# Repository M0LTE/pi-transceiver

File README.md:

# pi-transceiver
An attempt to build a complete ham radio transceiver around a Raspberry Pi

See [the wiki](https://github.com/M0LTE/pi-transceiver/wiki) for a more detailed project description / scratchlist of ideas / plans.

Also see [the open issues](https://github.com/M0LTE/pi-transceiver/issues) for stuff which needs working on. I've marked a few as Good First Issues.

[Discussions](https://github.com/M0LTE/pi-transceiver/discussions) is also a good place to ask questions / make comments / suggestions without raising an issue.

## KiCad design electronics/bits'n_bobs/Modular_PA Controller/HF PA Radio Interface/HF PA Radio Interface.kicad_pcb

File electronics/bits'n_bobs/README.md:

# Bits'n_bobs
This is a collection of small prototype modules and breakout boards to test various devices and features for the Pi Transceiver and similar projects.

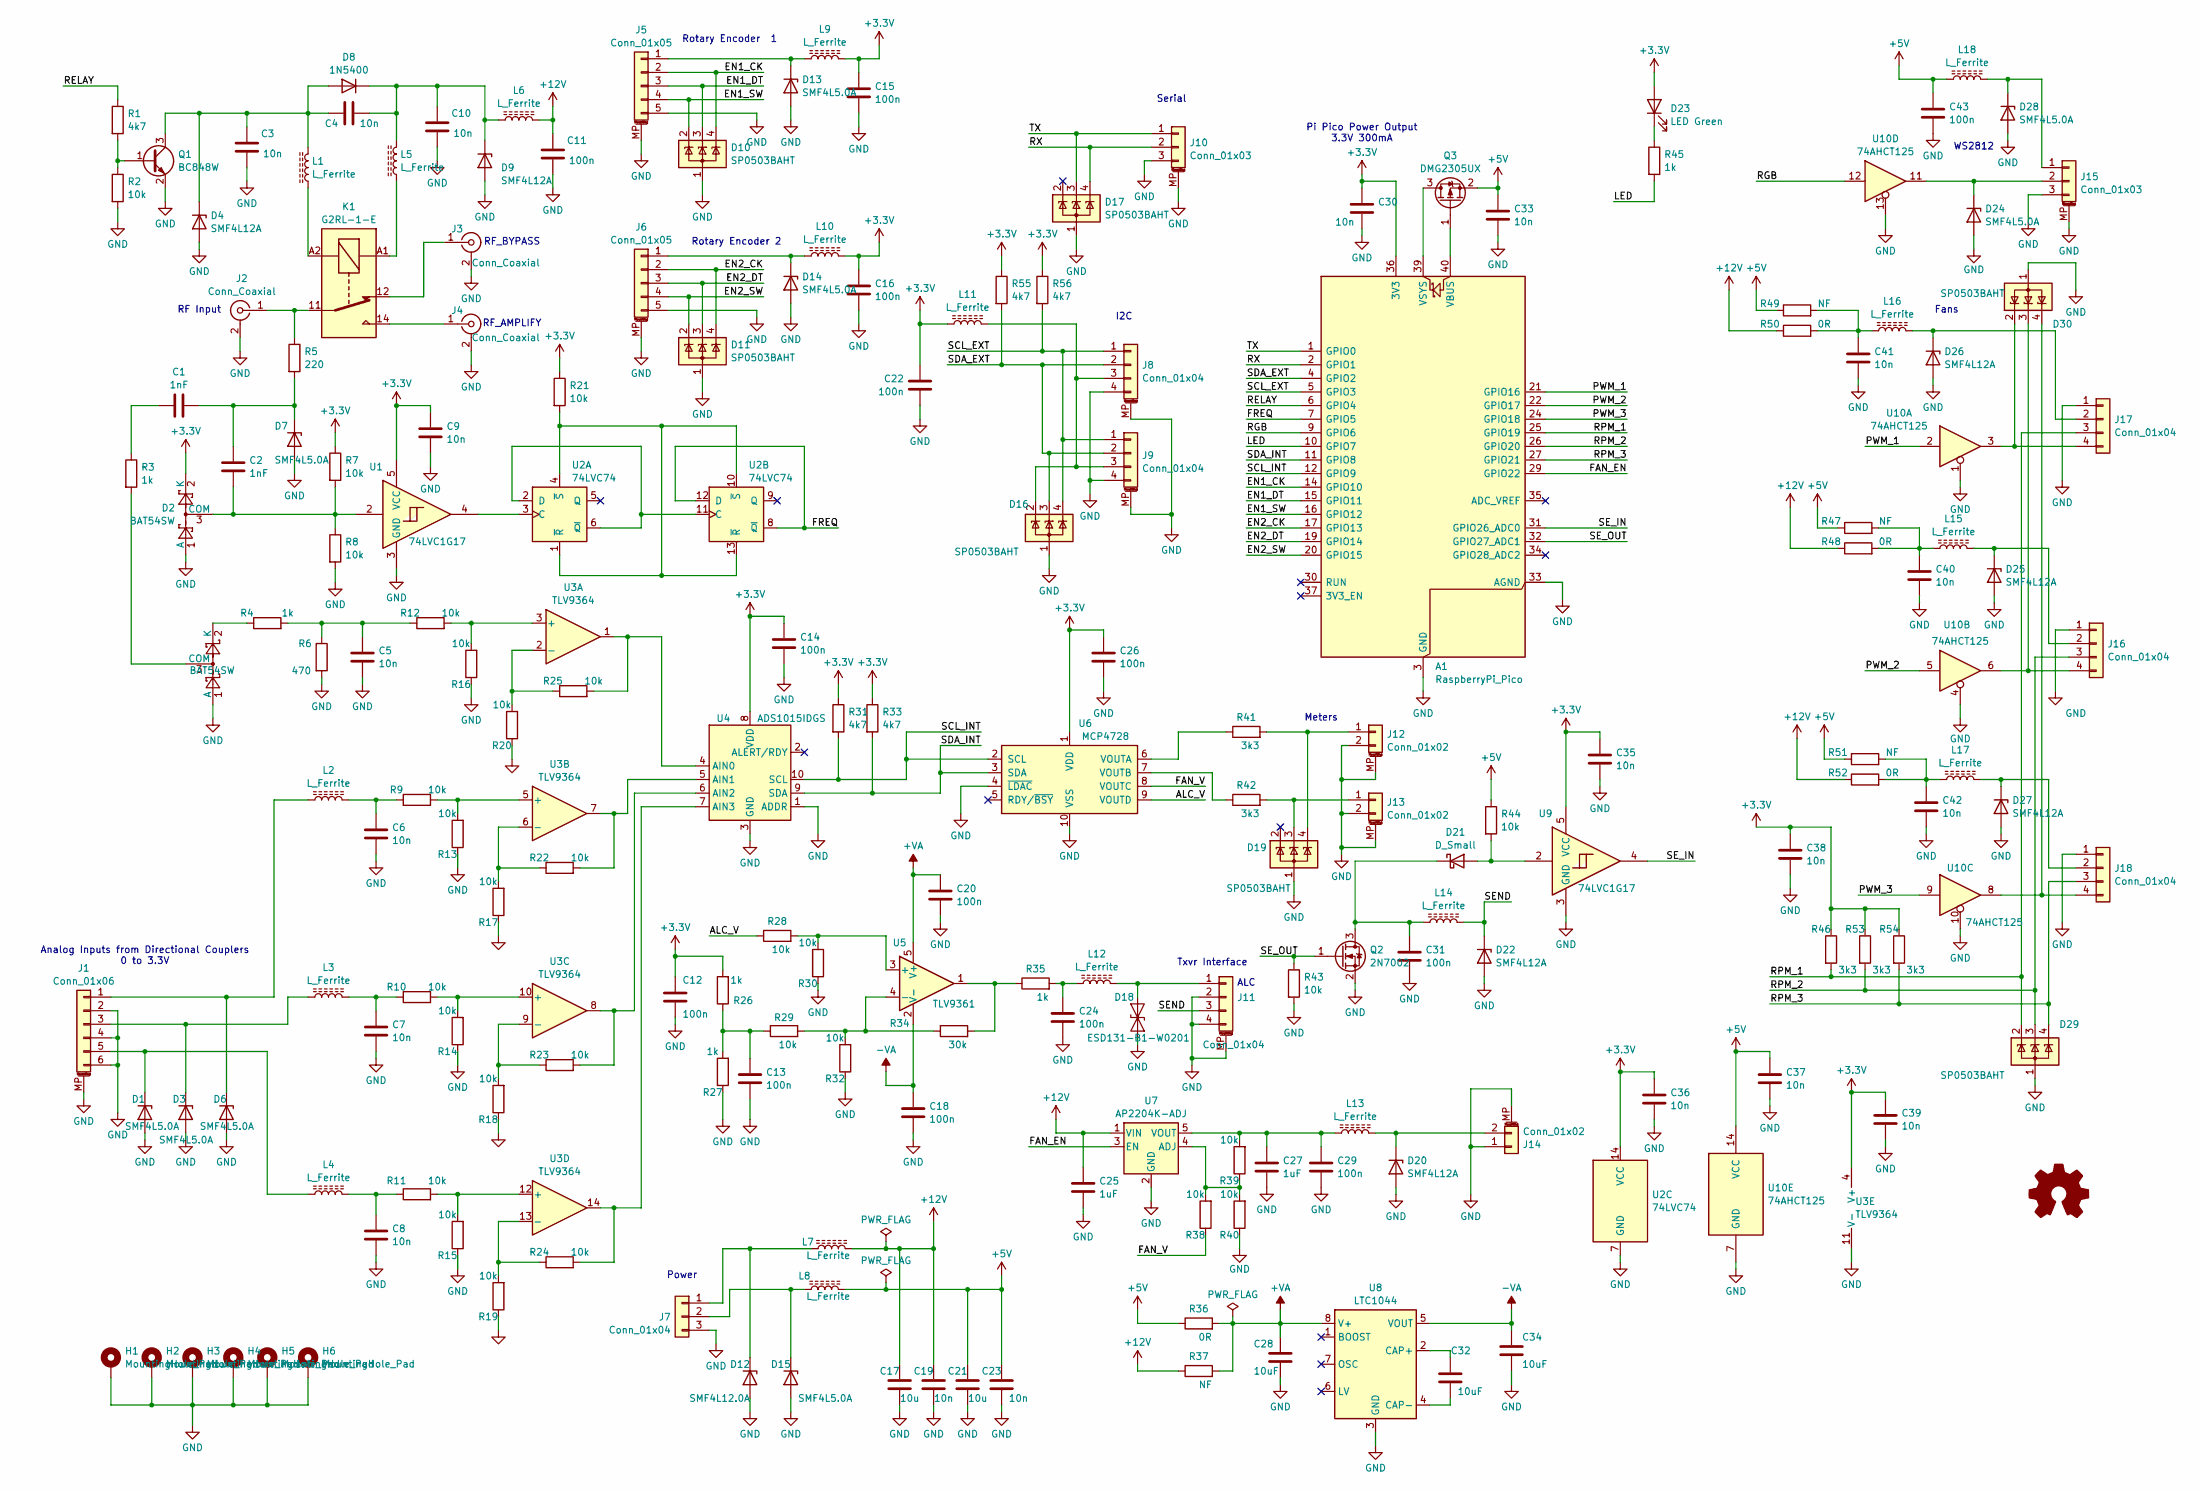
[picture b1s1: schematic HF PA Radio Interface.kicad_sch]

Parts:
A1: RaspberryPi_Pico; RPi_Pico_SMD_TH
C1, C2: 1nF; C_0603_1608Metric
C3, C4, C5, C6, C7, C8, C9, C10, C19, C23, C30, C33, C35, C36, C37, C38, C39, C40, C41, C42: 10n; C_0603_1608Metric
C11, C12, C13, C14, C15, C16, C18, C20, C22, C24, C26, C29, C31, C43: 100n; C_0603_1608Metric
C17, C21: 10u; C_0805_2012Metric
C25, C27: 1uF; C_0603_1608Metric
C28, C32, C34: 10uF; C_0603_1608Metric
D1, D3, D6, D7, D13, D14, D15, D24, D28: SMF4L5.0A; D_SOD-523
D2, D5: BAT54SW; SOT-323_SC-70
D4, D9, D20, D22, D25, D26, D27: SMF4L12A; D_SOD-523
D8: 1N5400; D_SOD-123
D10, D11, D16, D17, D19, D29, D30: SP0503BAHT; SOT-143
D12: SMF4L12.0A; D_SOD-523
D18: ESD131-B1-W0201; D_SOD-523
D21: D_Small; D_SOD-323
D23: LED Green; LED_0603_1608Metric
H1, H2, H3, H4, H5, H6: MountingHole_Pad; MountingHole_3.2mm_M3_DIN965_Pad
J1: Conn_01x06; JST_PH_S6B-PH-SM4-TB_1x06-1MP_P2.00mm_Horizontal
J2, J3, J4: Conn_Coaxial; SMA_Samtec_SMA-J-P-X-ST-EM1_EdgeMount
J5, J6: Conn_01x05; JST_PH_B5B-PH-SM4-TB_1x05-1MP_P2.00mm_Vertical
J7: Conn_01x04; JST_XH_S3B-XH-A_1x03_P2.50mm_Horizontal
J8, J9, J11: Conn_01x04; JST_PH_B4B-PH-SM4-TB_1x04-1MP_P2.00mm_Vertical
J10: Conn_01x03; JST_PH_B3B-PH-SM4-TB_1x03-1MP_P2.00mm_Vertical
J12, J13: Conn_01x02; JST_PH_B2B-PH-SM4-TB_1x02-1MP_P2.00mm_Vertical
J14: Conn_01x02; JST_PH_S2B-PH-SM4-TB_1x02-1MP_P2.00mm_Horizontal
J15: Conn_01x03; JST_PH_S3B-PH-SM4-TB_1x03-1MP_P2.00mm_Horizontal
J16, J17, J18: Conn_01x04; KF2510-4AW_3+1P
K1: G2RL-1-E; Relay_SPDT_Omron_G2RL-1-E
L1, L2, L3, L4, L5, L6, L7, L8, L9, L10, L11, L12, L13, L14, L15, L16, L17, L18: L_Ferrite; L_0603_1608Metric
Q1: BC848W; SOT-323_SC-70
Q2: 2N7002; SOT-23
Q3: DMG2305UX; SOT-23
R1, R31, R33, R55, R56: 4k7; R_0603_1608Metric
R2, R7, R8, R9, R10, R11, R12, R13, R14, R15, R16, R17, R18, R19, R20, R21, R22, R23, R24, R25, R28, R29, R30, R32, R38, R39, R40, R43, R44: 10k; R_0603_1608Metric
R3, R4, R26, R27, R35, R45: 1k; R_0603_1608Metric
R5: 220; R_0603_1608Metric
R6: 470; R_0603_1608Metric
R34: 30k; R_0603_1608Metric
R36, R48, R50, R52: 0R; R_0603_1608Metric
R37, R47, R49, R51: NF; R_0603_1608Metric
R41, R42, R46, R53, R54: 3k3; R_0603_1608Metric
SYM1: Logo_Open_Hardware_Small; OSHW-Logo2_7.3x6mm_SilkScreen
U1, U9: 74LVC1G17; SOT-353_SC-70-5
U2: 74LVC74; SOIC-14_3.9x8.7mm_P1.27mm
U3: TLV9364; SOIC-14_3.9x8.7mm_P1.27mm
U4: ADS1015IDGS; TSSOP-10_3x3mm_P0.5mm
U5: TLV9361; SOT-23-5
U6: MCP4728; MSOP-10_3x3mm_P0.5mm
U7: AP2204K-ADJ; SOT-23-5
U8: LTC1044; SOIC-8_5.23x5.23mm_P1.27mm
U10: 74AHCT125; TSSOP-14_4.4x5mm_P0.65mm

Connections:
+3.3V: A1.36 (3V3), C9.1, C12.1, C14.1, C15.1, C16.1, C22.1, C26.1, C30.1, C35.1, C36.1, C38.1, C39.1, D2.2 (K), D23.2 (A), L9.2, L10.2, L11.2, R7.1, R21.1, R26.2, R31.1, R33.1, R46.1, R53.1, R54.1, R55.1, R56.1, U1.5 (VCC), U2.14 (VCC), U3.4 (V+), U4.8 (VDD), U6.1 (VDD), U9.5 (VCC)
+5V: C21.1, C23.1, C33.1, C37.1, C43.1, L8.2, L18.1, Q3.2 (S), R36.1, R44.1, R47.1, R49.1, R51.1, U10.14 (VCC)
+12V: C11.1, C17.1, C19.1, C25.1, L6.2, L7.2, R37.1, R48.1, R50.1, R52.1, U7.1 (VIN)
+VA: C20.1, C28.1, R36.2, R37.2, U5.5 (V+), U8.8 (V+)
-VA: C18.1, C34.1, U5.2 (V-), U8.5 (VOUT)
/ALC_V: R28.1, U6.9 (VOUTD)
/EN1_CK: A1.14 (GPIO10), D10.4 (K), J5.2
/EN1_DT: A1.15 (GPIO11), D10.3 (K), J5.3
/EN1_SW: A1.16 (GPIO12), D10.2 (K), J5.4
/EN2_CK: A1.17 (GPIO13), D11.4 (K), J6.2
/EN2_DT: A1.19 (GPIO14), D11.3 (K), J6.3
/EN2_SW: A1.20 (GPIO15), D11.2 (K), J6.4
/FAN_EN: A1.29 (GPIO22), U7.3 (EN)
/FAN_V: R38.1, U6.8 (VOUTC)
/FREQ: A1.7 (GPIO5), U2.8 (~Q), U2.12 (D)
/LED: A1.10 (GPIO7), R45.2
/PWM_1: A1.21 (GPIO16), U10.2
/PWM_2: A1.22 (GPIO17), U10.5
/PWM_3: A1.24 (GPIO18), U10.9
/RELAY: A1.6 (GPIO4), R1.1
/RGB: A1.9 (GPIO6), U10.12
/RPM_1: A1.25 (GPIO19), D29.2 (K), J17.3, R46.2
/RPM_2: A1.26 (GPIO20), D29.3 (K), J16.3, R53.2
/RPM_3: A1.27 (GPIO21), D29.4 (K), J18.3, R54.2
/RX: A1.2 (GPIO1), D17.4 (K), J10.2
/SCL_EXT: A1.5 (GPIO3), D16.4 (K), J8.1, J9.1, R56.2
/SCL_INT: A1.12 (GPIO9), R31.2, U4.10 (SCL), U6.2 (SCL)
/SDA_EXT: A1.4 (GPIO2), D16.3 (K), J8.2, J9.2, R55.2
/SDA_INT: A1.11 (GPIO8), R33.2, U4.9 (SDA), U6.3 (SDA)
/SEND: D22.1 (K), J11.3, L14.2
/SE_IN: A1.31 (GPIO26_ADC0), U9.4
/SE_OUT: A1.32 (GPIO27_ADC1), Q2.1 (G), R43.1
/TX: A1.1 (GPIO0), D17.3 (K), J10.1
GND: A1.3 (GND), A1.8 (GND), A1.13 (GND), A1.18 (GND), A1.23 (GND), A1.28 (GND), A1.33 (AGND), A1.38 (GND), C3.2, C5.2, C6.2, C7.2, C8.2, C9.2, C10.2, C11.2, C12.2, C13.2, C14.2, C15.2, C16.2, C17.2, C18.2, C19.2, C20.2, C21.2, C22.2, C23.2, C24.2, C25.2, C26.2, C27.2, C28.2, C29.2, C30.2, C31.2, C33.2, C34.2, C35.2, C36.2, C37.2, C38.2, C39.2, C40.2, C41.2, C42.2, C43.2, D1.2 (A), D2.1 (A), D3.2 (A), D4.2 (A), D5.1 (A), D6.2 (A), D7.2 (A), D9.2 (A), D10.1 (A), D11.1 (A), D12.2 (A), D13.2 (A), D14.2 (A), D15.2 (A), D16.1 (A), D17.1 (A), D18.1 (A1), D19.1 (A), D20.2 (A), D22.2 (A), D24.2 (A), D25.2 (A), D26.2 (A), D27.2 (A), D28.2 (A), D29.1 (A), D30.1 (A), H1.1, H2.1, H3.1, H4.1, H5.1, H6.1, J1.2, J1.4, J1.6, J1.MP (MountPin), J2.2 (Ext), J3.2 (Ext), J4.2 (Ext), J5.5, J5.MP (MountPin), J6.5, J6.MP (MountPin), J7.3, J8.4, J8.MP (MountPin), J9.4, J9.MP (MountPin), J10.3, J10.MP (MountPin), J11.2, J11.4, J11.MP (MountPin), J12.2, J12.MP (MountPin), J13.2, J13.MP (MountPin), J14.1, J14.MP (MountPin), J15.3, J15.MP (MountPin), J16.1, J17.1, J18.1, Q1.2 (E), Q2.2 (S), R2.2, R6.2, R8.2, R13.1, R14.1, R15.1, R16.1, R17.1, R18.1, R19.1, R20.1, R27.1, R30.1, R32.1, R40.1, R43.2, U1.3 (GND), U2.7 (GND), U3.11 (V-), U4.1 (ADDR), U4.3 (GND), U6.4 (~LDAC), U6.10 (VSS), U7.2 (GND), U8.3 (GND), U9.3 (GND), U10.1, U10.4, U10.7 (GND), U10.10, U10.13
unnamed: A1.40 (VBUS), Q3.1 (G)
unnamed: A1.39 (VSYS), Q3.3 (D)
unnamed: C1.2, R3.1
unnamed: C5.1, R4.2, R6.1, R12.1
unnamed: C6.1, L2.2, R9.1
unnamed: C7.1, L3.2, R10.1
unnamed: C8.1, L4.2, R11.1
unnamed: C13.1, R26.1, R27.2, R29.1
unnamed: C24.1, L12.1, R35.2
unnamed: C40.1, L15.1, R47.2, R48.2
unnamed: C41.1, L16.1, R49.2, R50.2
unnamed: C42.1, L17.1, R51.2, R52.2
unnamed: D1.1 (K), J1.5, L4.1
unnamed: C2.2, D2.3 (COM), R7.2, R8.1, U1.2
unnamed: D3.1 (K), J1.3, L3.1
unnamed: C3.1, C4.1, D4.1 (K), D8.2 (A), L1.2, Q1.3 (C)
unnamed: D5.3 (COM), R3.2
unnamed: D5.2 (K), R4.1
unnamed: D6.1 (K), J1.1, L2.1
unnamed: C1.1, C2.1, D7.1 (K), R5.2
unnamed: C4.2, C10.1, D8.1 (K), D9.1 (K), L5.2, L6.1
unnamed: D12.1 (K), J7.1, L7.1
unnamed: D13.1 (K), J5.1, L9.1
unnamed: D14.1 (K), J6.1, L10.1
unnamed: D15.1 (K), J7.2, L8.1
unnamed: D18.2 (A2), J11.1, L12.2
unnamed: D20.1 (K), J14.2, L13.2
unnamed: D21.2 (A), R44.2, U9.2
unnamed: C31.1, D21.1 (K), L14.1, Q2.3 (D)
unnamed: D23.1 (K), R45.1
unnamed: D24.1 (K), J15.2, U10.11
unnamed: D25.1 (K), J16.2, L15.2
unnamed: D26.1 (K), J17.2, L16.2
unnamed: D27.1 (K), J18.2, L17.2
unnamed: D28.1 (K), J15.1, L18.2
unnamed: J2.1 (In), K1.11, R5.1
unnamed: J3.1 (In), K1.12
unnamed: J4.1 (In), K1.14
unnamed: D16.2 (K), J8.3, J9.3, L11.1
unnamed: D19.4 (K), J12.1, R41.2
unnamed: D19.3 (K), J13.1, R42.2
unnamed: D30.3 (K), J16.4, U10.6
unnamed: D30.2 (K), J17.4, U10.3
unnamed: D30.4 (K), J18.4, U10.8
unnamed: K1.A1, L5.1
unnamed: K1.A2, L1.1
unnamed: Q1.1 (B), R1.2, R2.1
unnamed: R34.2, R35.1, U5.1
unnamed: U1.4, U2.3 (C)
unnamed: U2.2 (D), U2.6 (~Q), U2.11 (C)
unnamed: R21.2, U2.1 (~R), U2.4 (~S), U2.10 (~S), U2.13 (~R)
unnamed: R12.2, R16.2, U3.3 (+)
unnamed: R20.2, R25.1, U3.2 (-)
unnamed: R9.2, R13.2, U3.5 (+)
unnamed: R17.2, R22.1, U3.6 (-)
unnamed: R10.2, R14.2, U3.10 (+)
unnamed: R18.2, R23.1, U3.9 (-)
unnamed: R11.2, R15.2, U3.12 (+)
unnamed: R19.2, R24.1, U3.13 (-)
unnamed: R25.2, U3.1, U4.4 (AIN0)
unnamed: R22.2, U3.7, U4.5 (AIN1)
unnamed: R23.2, U3.8, U4.6 (AIN2)
unnamed: R24.2, U3.14, U4.7 (AIN3)
unnamed: R28.2, R30.2, U5.3 (+)
unnamed: R29.2, R32.2, R34.1, U5.4 (-)
unnamed: R41.1, U6.6 (VOUTA)
unnamed: R42.1, U6.7 (VOUTB)
unnamed: R38.2, R39.1, R40.2, U7.4 (ADJ)
unnamed: C27.1, C29.1, L13.1, R39.2, U7.5 (VOUT)
unnamed: C32.1, U8.2 (CAP+)
unnamed: C32.2, U8.4 (CAP-)

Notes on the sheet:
Rotary Encoder 2
RF Input
Fans
Txvr Interface
ALC
RF_BYPASS
Serial
RF_AMPLIFY
Rotary Encoder 1
Analog Inputs from Directional Couplers 0 to 3.3V
Power
Meters
WS2812
Pi Pico Power Output 3.3V 300mA
I2C

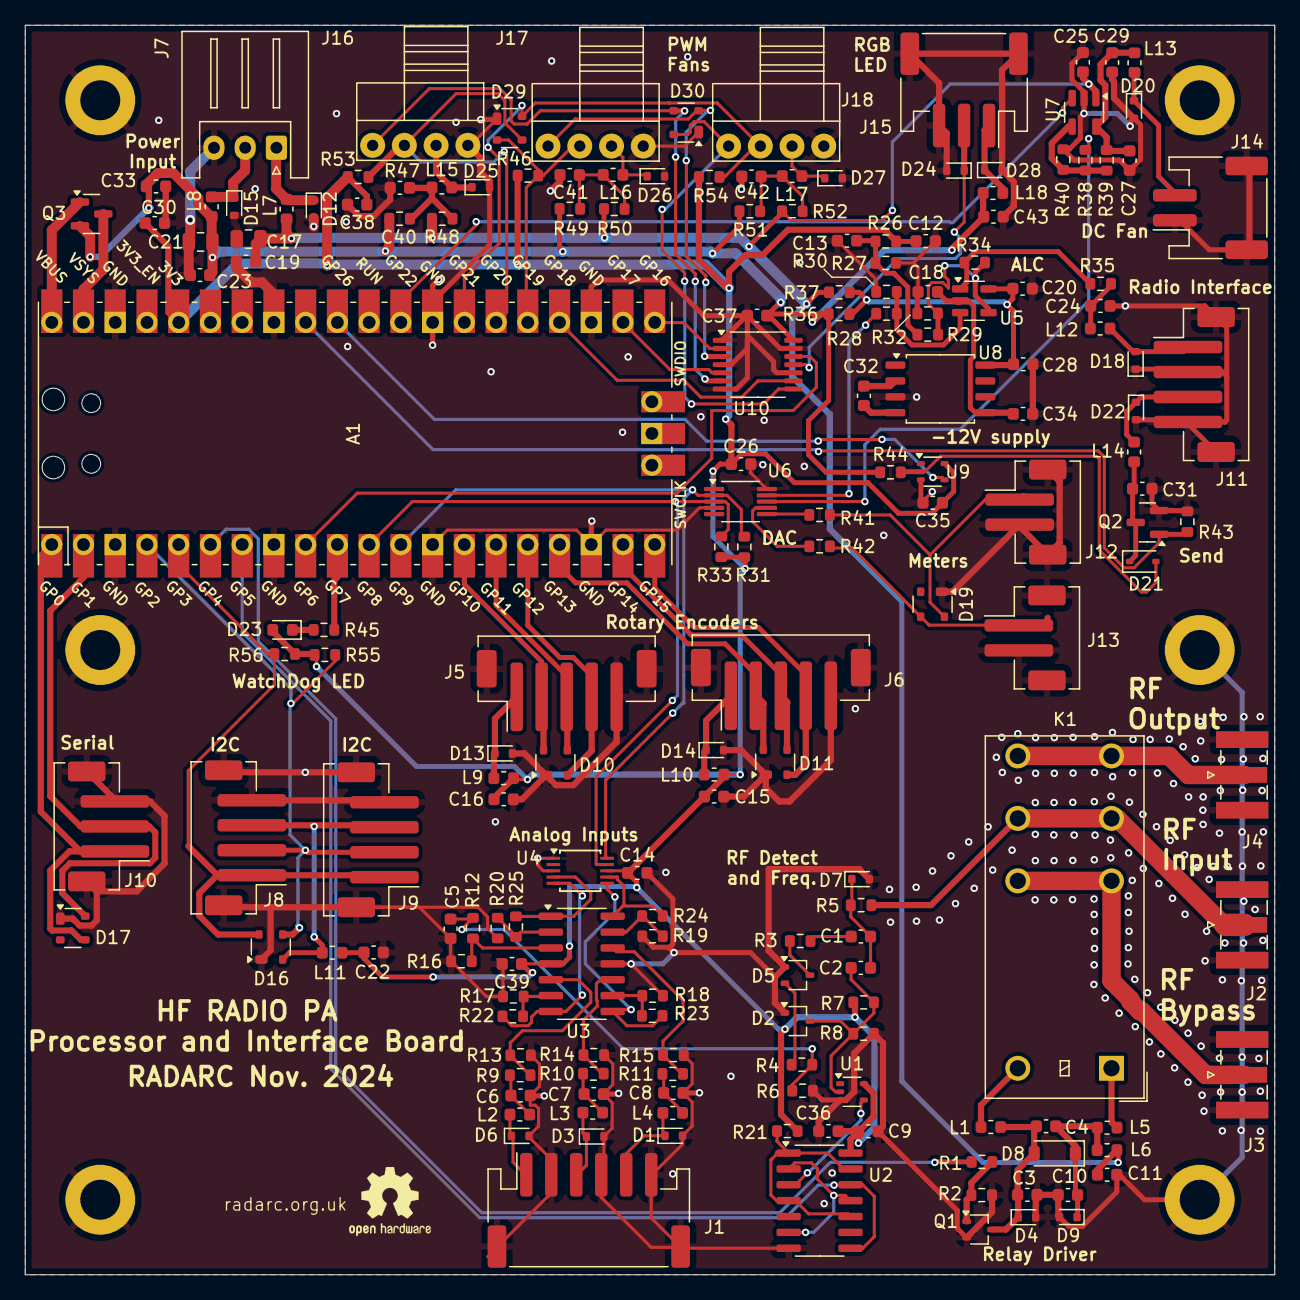
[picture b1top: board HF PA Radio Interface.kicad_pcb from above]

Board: 2 copper layers, 100.0 x 100.0 mm, 187 parts (0 on the bottom side), 105 nets.

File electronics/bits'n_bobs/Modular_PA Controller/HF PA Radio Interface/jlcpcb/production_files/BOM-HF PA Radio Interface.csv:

Comment,Designator,Footprint,LCSC
Conn_Coaxial,"J2,J3,J4",SMA_Samtec_SMA-J-P-X-ST-EM1_EdgeMount,C1509221
10k,R22,R_0603_1608Metric,
10k,R29,R_0603_1608Metric,
LTC1044,U8,SOIC-8_5.23x5.23mm_P1.27mm,
10n,C5,C_0603_1608Metric,
L_Ferrite,L17,L_0603_1608Metric,
10uF,C28,C_0603_1608Metric,
MCP4728,U6,MSOP-10_3x3mm_P0.5mm,
G2RL-1-E,K1,Relay_SPDT_Omron_G2RL-1-E,
10k,R9,R_0603_1608Metric,
3k3,R42,R_0603_1608Metric,
10k,R12,R_0603_1608Metric,
1N5400,D8,D_SOD-123,
SP0503BAHT,D10,SOT-143,
Conn_01x04,J7,JST_XH_S3B-XH-A_1x03_P2.50mm_Horizontal,
NF,R47,R_0603_1608Metric,
30k,R34,R_0603_1608Metric,
0R,R52,R_0603_1608Metric,
3k3,R53,R_0603_1608Metric,
Conn_01x03,J15,JST_PH_S3B-PH-SM4-TB_1x03-1MP_P2.00mm_Horizontal,
1k,R26,R_0603_1608Metric,
L_Ferrite,L4,L_0603_1608Metric,
100n,C14,C_0603_1608Metric,
10k,R30,R_0603_1608Metric,
10k,R11,R_0603_1608Metric,
1k,R27,R_0603_1608Metric,
100n,C31,C_0603_1608Metric,
D_Small,D21,D_SOD-323,
Conn_01x04,J9,JST_PH_B4B-PH-SM4-TB_1x04-1MP_P2.00mm_Vertical,
SP0503BAHT,D19,SOT-143,
NF,R49,R_0603_1608Metric,
Conn_01x04,J8,JST_PH_B4B-PH-SM4-TB_1x04-1MP_P2.00mm_Vertical,
10k,R40,R_0603_1608Metric,
L_Ferrite,L2,L_0603_1608Metric,
10n,C38,C_0603_1608Metric,
Conn_01x04,J16,KF2510-4AW_3+1P,
Conn_01x05,J6,JST_PH_B5B-PH-SM4-TB_1x05-1MP_P2.00mm_Vertical,
SP0503BAHT,D17,SOT-143,
4k7,R56,R_0603_1608Metric,
Conn_01x03,J10,JST_PH_B3B-PH-SM4-TB_1x03-1MP_P2.00mm_Vertical,
SMF4L12A,D27,D_SOD-523,
10k,R8,R_0603_1608Metric,
Conn_01x04,J18,KF2510-4AW_3+1P,
10k,R18,R_0603_1608Metric,
74LVC1G17,U9,SOT-353_SC-70-5,
10k,R13,R_0603_1608Metric,
10k,R10,R_0603_1608Metric,
L_Ferrite,L8,L_0603_1608Metric,
L_Ferrite,L12,L_0603_1608Metric,
L_Ferrite,L16,L_0603_1608Metric,
4k7,R33,R_0603_1608Metric,
10n,C23,C_0603_1608Metric,
100n,C24,C_0603_1608Metric,
L_Ferrite,L6,L_0603_1608Metric,
4k7,R31,R_0603_1608Metric,
RaspberryPi_Pico,A1,RPi_Pico_SMD_TH,
AP2204K-ADJ,U7,SOT-23-5,
SMF4L12A,D25,D_SOD-523,
10uF,C34,C_0603_1608Metric,
10k,R16,R_0603_1608Metric,
10n,C39,C_0603_1608Metric,
BAT54SW,D5,SOT-323_SC-70,
SMF4L12A,D4,D_SOD-523,
3k3,R41,R_0603_1608Metric,
Conn_01x06,J1,JST_PH_S6B-PH-SM4-TB_1x06-1MP_P2.00mm_Horizontal,
10n,C40,C_0603_1608Metric,
L_Ferrite,L15,L_0603_1608Metric,
100n,C12,C_0603_1608Metric,
SP0503BAHT,D29,SOT-143,
470,R6,R_0603_1608Metric,
100n,C16,C_0603_1608Metric,
10n,C4,C_0603_1608Metric,
100n,C26,C_0603_1608Metric,
2N7002,Q2,SOT-23,
10n,C42,C_0603_1608Metric,
10k,R23,R_0603_1608Metric,
L_Ferrite,L3,L_0603_1608Metric,
L_Ferrite,L14,L_0603_1608Metric,
SMF4L5.0A,D3,D_SOD-523,
SP0503BAHT,D16,SOT-143,
10n,C19,C_0603_1608Metric,
10n,C9,C_0603_1608Metric,
10k,R39,R_0603_1608Metric,
10n,C6,C_0603_1608Metric,
10n,C8,C_0603_1608Metric,
1k,R4,R_0603_1608Metric,
SMF4L12A,D26,D_SOD-523,
SMF4L5.0A,D24,D_SOD-523,
0R,R50,R_0603_1608Metric,
1uF,C25,C_0603_1608Metric,
10k,R43,R_0603_1608Metric,
Conn_01x05,J5,JST_PH_B5B-PH-SM4-TB_1x05-1MP_P2.00mm_Vertical,
10n,C33,C_0603_1608Metric,
10n,C35,C_0603_1608Metric,
L_Ferrite,L11,L_0603_1608Metric,
220,R5,R_0603_1608Metric,
L_Ferrite,L10,L_0603_1608Metric,
10k,R25,R_0603_1608Metric,
BAT54SW,D2,SOT-323_SC-70,
10k,R38,R_0603_1608Metric,
L_Ferrite,L1,L_0603_1608Metric,
SMF4L12A,D9,D_SOD-523,
Conn_01x02,J14,JST_PH_S2B-PH-SM4-TB_1x02-1MP_P2.00mm_Horizontal,
TLV9361,U5,SOT-23-5,
1nF,C2,C_0603_1608Metric,
LED Green,D23,LED_0603_1608Metric,
10n,C41,C_0603_1608Metric,
100n,C29,C_0603_1608Metric,
100n,C22,C_0603_1608Metric,
10k,R14,R_0603_1608Metric,
L_Ferrite,L9,L_0603_1608Metric,
100n,C18,C_0603_1608Metric,
SMF4L5.0A,D7,D_SOD-523,
SMF4L12A,D20,D_SOD-523,
10k,R21,R_0603_1608Metric,
10n,C37,C_0603_1608Metric,
L_Ferrite,L18,L_0603_1608Metric,
SMF4L5.0A,D6,D_SOD-523,
74LVC1G17,U1,SOT-353_SC-70-5,
3k3,R54,R_0603_1608Metric,
Conn_01x02,J13,JST_PH_B2B-PH-SM4-TB_1x02-1MP_P2.00mm_Vertical,
SP0503BAHT,D30,SOT-143,
NF,R51,R_0603_1608Metric,
L_Ferrite,L13,L_0603_1608Metric,
1k,R35,R_0603_1608Metric,
10k,R28,R_0603_1608Metric,
10u,C21,C_0805_2012Metric,
10n,C3,C_0603_1608Metric,
DMG2305UX,Q3,SOT-23,
1nF,C1,C_0603_1608Metric,
SMF4L5.0A,D1,D_SOD-523,
4k7,R1,R_0603_1608Metric,
3k3,R46,R_0603_1608Metric,
100n,C15,C_0603_1608Metric,
10n,C36,C_0603_1608Metric,
10uF,C32,C_0603_1608Metric,
100n,C20,C_0603_1608Metric,
10k,R24,R_0603_1608Metric,
10n,C7,C_0603_1608Metric,
SMF4L5.0A,D14,D_SOD-523,
10k,R15,R_0603_1608Metric,
SMF4L12A,D22,D_SOD-523,
10k,R20,R_0603_1608Metric,
L_Ferrite,L5,L_0603_1608Metric,
10k,R2,R_0603_1608Metric,
100n,C11,C_0603_1608Metric,
0R,R36,R_0603_1608Metric,
Conn_01x02,J12,JST_PH_B2B-PH-SM4-TB_1x02-1MP_P2.00mm_Vertical,
10k,R7,R_0603_1608Metric,
100n,C13,C_0603_1608Metric,
Conn_01x04,J17,KF2510-4AW_3+1P,
ADS1015IDGS,U4,TSSOP-10_3x3mm_P0.5mm,
4k7,R55,R_0603_1608Metric,
SP0503BAHT,D11,SOT-143,
0R,R48,R_0603_1608Metric,
ESD131-B1-W0201,D18,D_SOD-523,
SMF4L5.0A,D13,D_SOD-523,
10k,R19,R_0603_1608Metric,
TLV9364,U3,SOIC-14_3.9x8.7mm_P1.27mm,
10k,R32,R_0603_1608Metric,
10n,C10,C_0603_1608Metric,
SMF4L12.0A,D12,D_SOD-523,
SMF4L5.0A,D28,D_SOD-523,
SMF4L5.0A,D15,D_SOD-523,
10u,C17,C_0805_2012Metric,
10n,C30,C_0603_1608Metric,
L_Ferrite,L7,L_0603_1608Metric,
BC848W,Q1,SOT-323_SC-70,
1k,R45,R_0603_1608Metric,
NF,R37,R_0603_1608Metric,
100n,C43,C_0603_1608Metric,
74LVC74,U2,SOIC-14_3.9x8.7mm_P1.27mm,
74AHCT125,U10,TSSOP-14_4.4x5mm_P0.65mm,
1k,R3,R_0603_1608Metric,
10k,R44,R_0603_1608Metric,
1uF,C27,C_0603_1608Metric,
10k,R17,R_0603_1608Metric,
Conn_01x04,J11,JST_PH_B4B-PH-SM4-TB_1x04-1MP_P2.00mm_Vertical,

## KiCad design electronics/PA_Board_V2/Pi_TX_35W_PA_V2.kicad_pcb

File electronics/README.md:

# pi-transceiver / electronics
Here is a folder for electronics parts of the Pi transceiver, e.g. PCBs

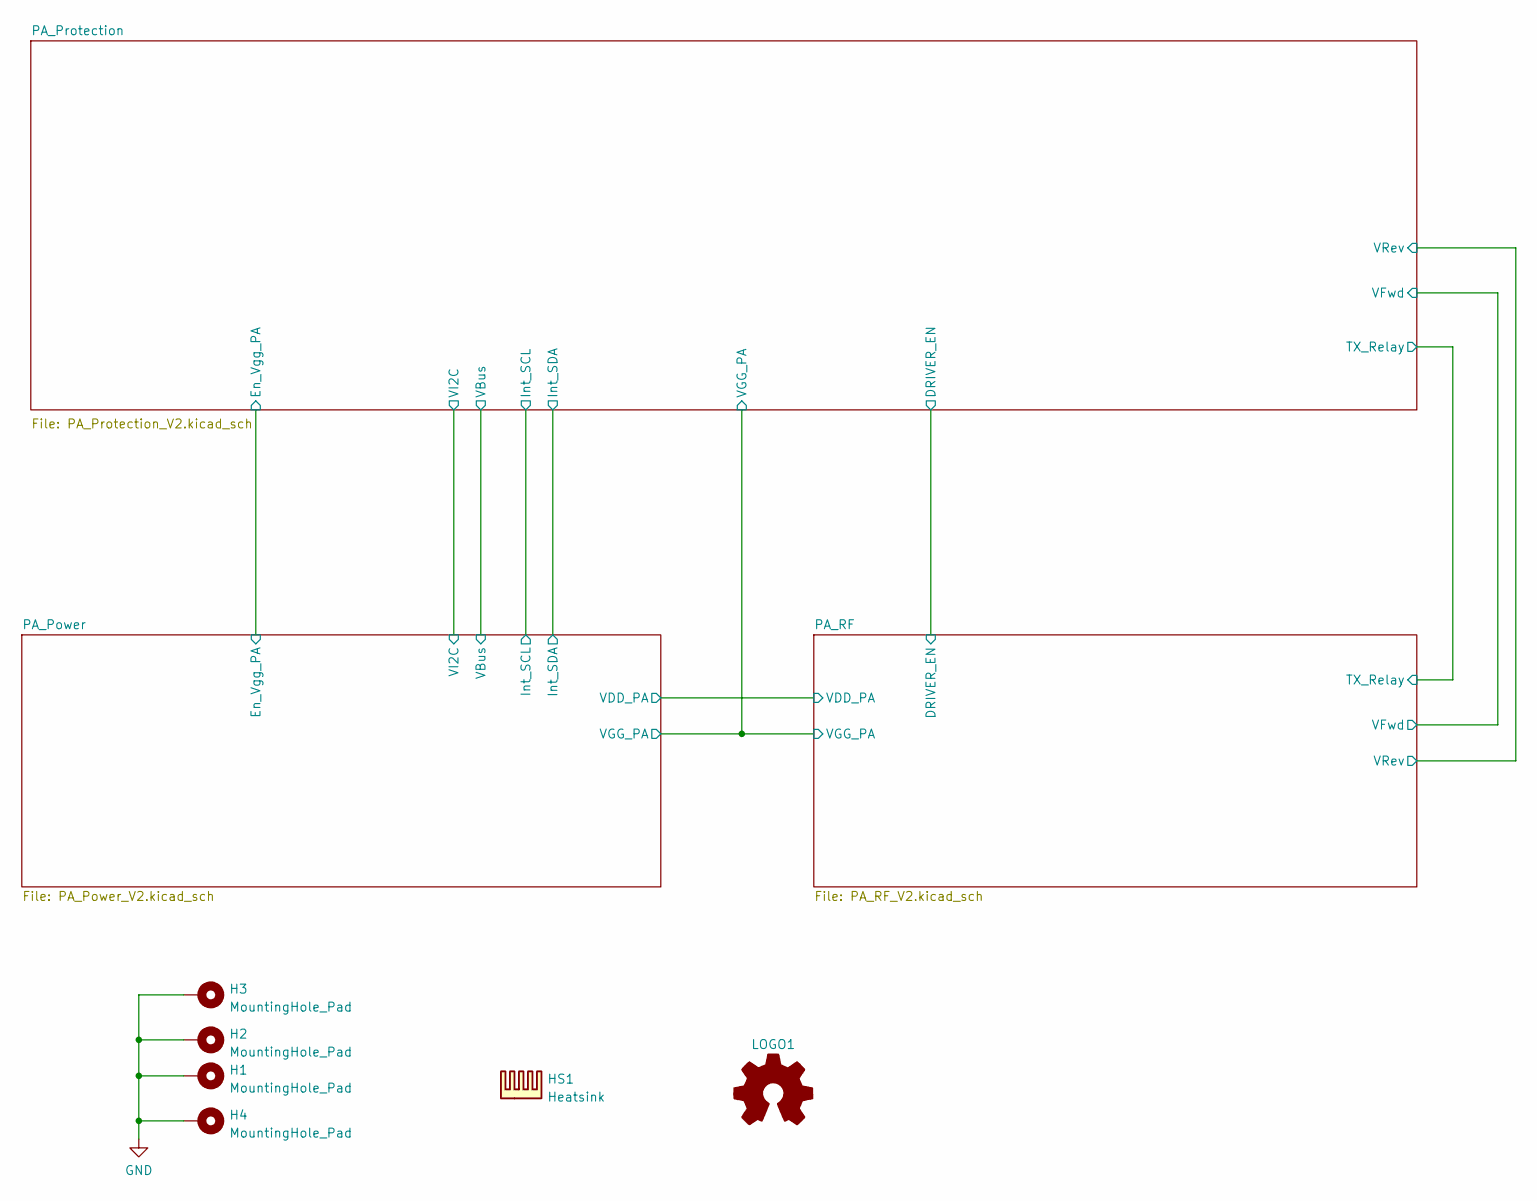
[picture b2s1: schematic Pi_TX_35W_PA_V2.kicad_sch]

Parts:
H1, H2, H3, H4: MountingHole_Pad; MountingHole_3.2mm_M3_DIN965_Pad
HS1: Heatsink; Copper_Pad
LOGO1: Logo_Open_Hardware_Small; OSHW-Logo2_9.8x8mm_SilkScreen

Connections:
GND: H1.1, H2.1, H3.1, H4.1; also elsewhere on the board

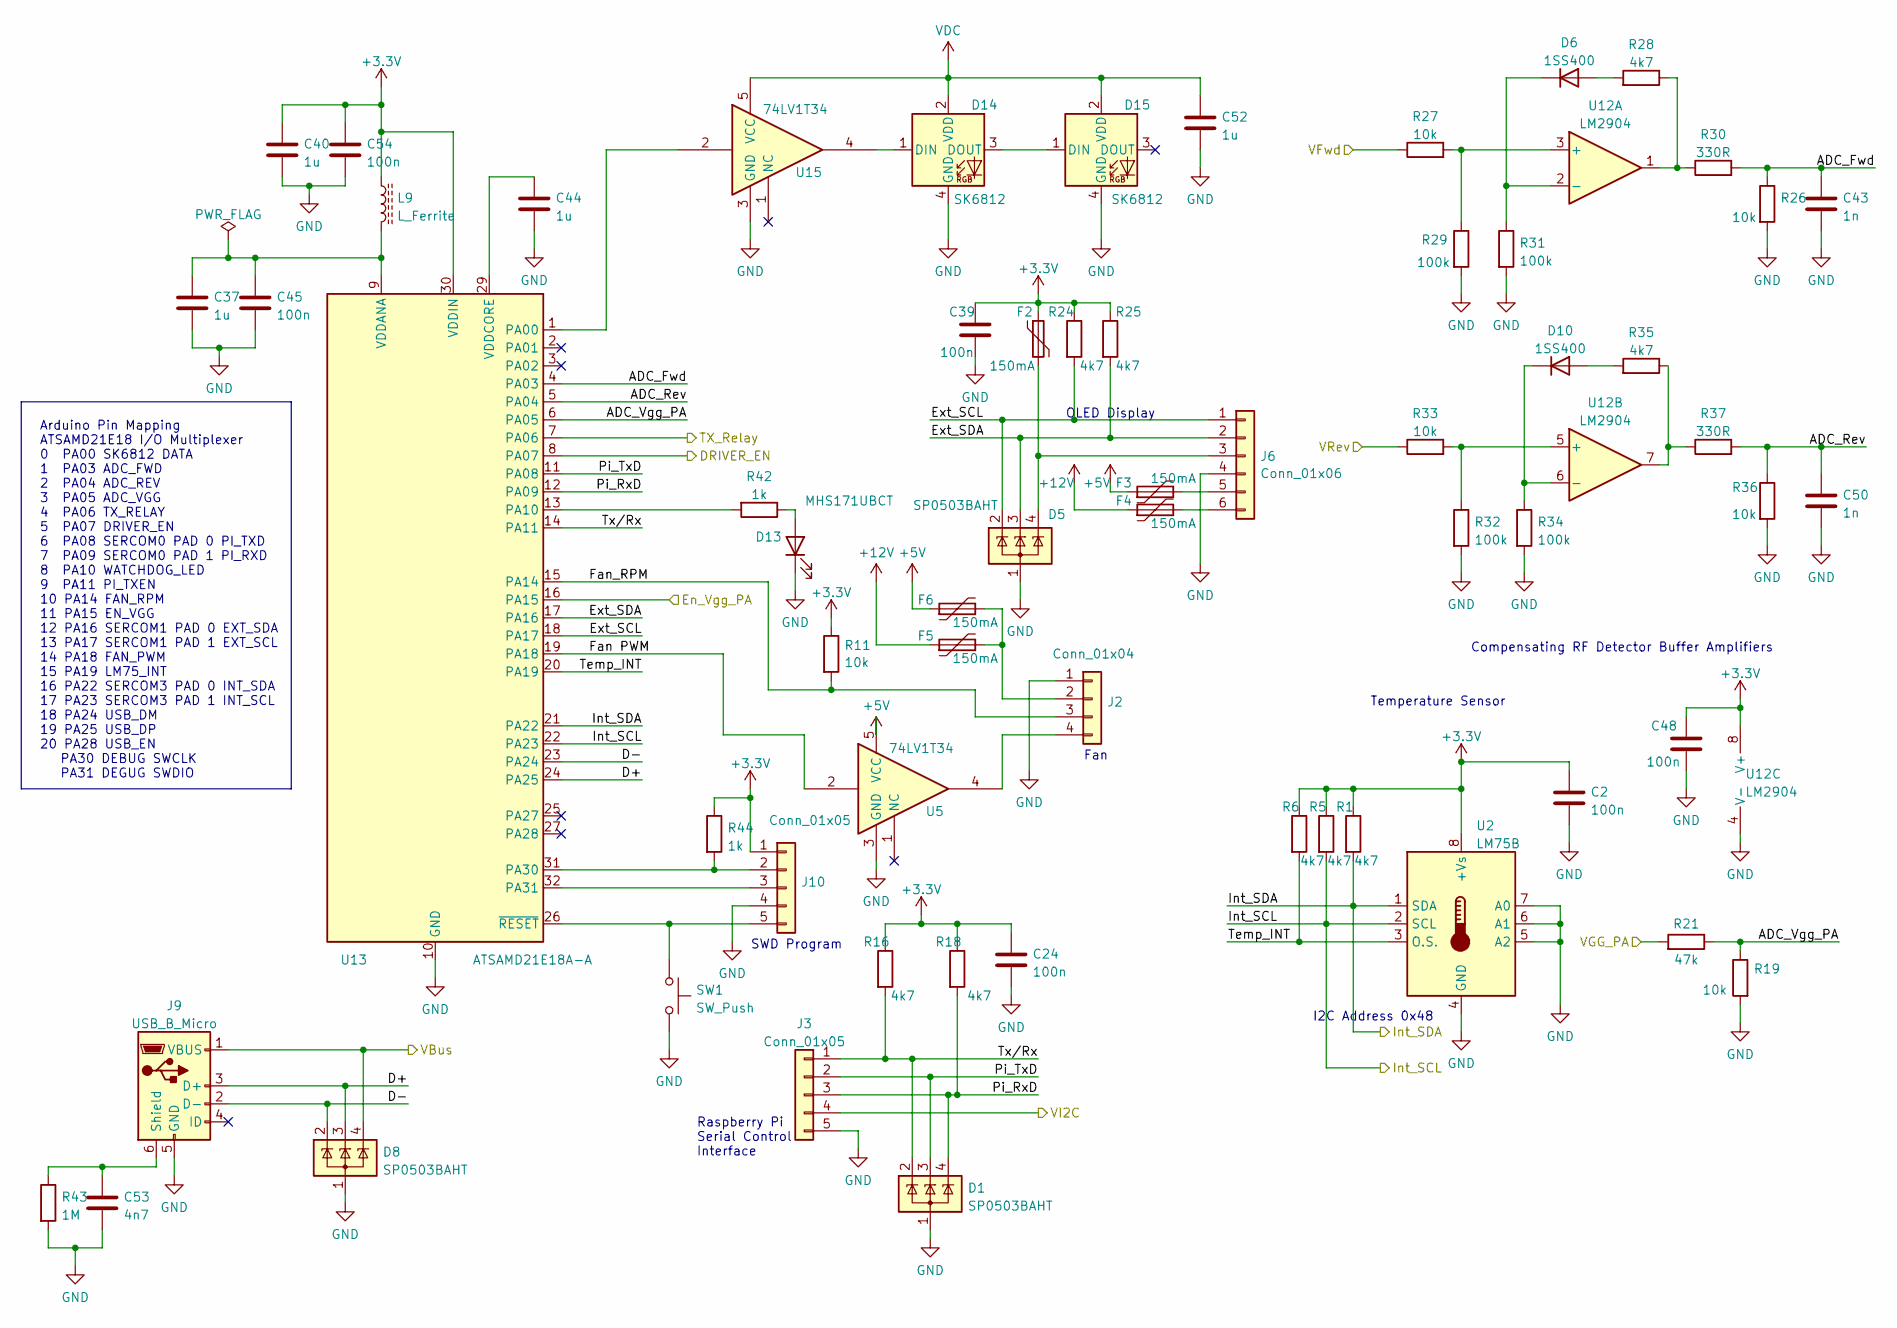
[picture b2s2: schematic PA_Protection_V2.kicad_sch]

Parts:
C2, C24, C39, C45, C48, C54: 100n; C_0603_1608Metric; LCSC Part C88136
C37, C40, C44, C52: 1u; C_0603_1608Metric; LCSC Part C89376
C43, C50: 1n; C_0603_1608Metric; LCSC Part C2839443
C53: 4n7; C_0603_1608Metric; LCSC Part C576815
D1, D5, D8: SP0503BAHT; SOT-143; LCSC Part C2682275
D6, D10: 1SS400; D_SOD-523; LCSC Part C68951
D13: MHS171UBCT; MHS171; LCSC Part C693906
D14, D15: SK6812; SK6812SIDE-A-RVS; LCSC Part C2890037
F2, F3, F4, F5, F6: 150mA; Fuse_0805_2012Metric; LCSC Part C2840556
J2: Conn_01x04; KF2510-4AW_3+1P
J3: Conn_01x05; JST_PH_S5B-PH-SM4-TB_1x05-1MP_P2.00mm_Horizontal; LCSC Part C7429692
J6: Conn_01x06; JST_PH_S6B-PH-SM4-TB_1x06-1MP_P2.00mm_Horizontal; LCSC Part C7429693
J9: USB_B_Micro; USB_Micro-B_Molex-105017-0001; LCSC Part C136000
J10: Conn_01x05; Debug_Clip
L9: L_Ferrite; L_0603_1608Metric; LCSC Part C98298
R1, R5, R6, R16, R18, R24, R25, R28, R35: 4k7; R_0603_1608Metric; LCSC Part C23162
R11, R19, R26, R27, R33, R36: 10k; R_0603_1608Metric; LCSC Part C25804
R21: 47k; R_0603_1608Metric; LCSC Part C25819
R29, R31, R32, R34: 100k; R_0603_1608Metric; LCSC Part C25803
R30, R37: 330R; R_0603_1608Metric; LCSC Part C23138
R42, R44: 1k; R_0603_1608Metric; LCSC Part C21190
R43: 1M; R_0603_1608Metric; LCSC Part C22935
SW1: SW_Push; Panasonic_EVQPUK_EVQPUB; LCSC Part C526225
U2: LM75B; SOIC-8_3.9x4.9mm_P1.27mm; LCSC Part C725792
U5, U15: 74LV1T34; SOT-353_SC-70-5; LCSC Part C5199768
U12: LM2904; SOIC-8_3.9x4.9mm_P1.27mm; LCSC Part C2941725
U13: ATSAMD21E18A-A; TQFP-32_7x7mm_P0.8mm; LCSC Part C618770

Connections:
+3.3V: C2.1, C24.1, C39.1, C40.1, C48.1, C54.1, F2.1, J10.1, L9.1, R1.1, R5.1, R6.1, R11.1, R16.1, R18.1, R24.1, R25.1, R44.1, U2.8 (+Vs), U12.8 (V+), U13.30 (VDDIN); also elsewhere on the board
+5V: F3.1, F6.1, U5.5 (VCC); also elsewhere on the board
+12V: F4.1, F5.1; also elsewhere on the board
/PA_Power/En_Vgg_PA: U13.16 (PA15); also elsewhere on the board
/PA_Power/Int_SCL: R5.2, U2.2 (SCL), U13.22 (PA23); also elsewhere on the board
/PA_Power/Int_SDA: R1.2, U2.1 (SDA), U13.21 (PA22); also elsewhere on the board
/PA_Power/VBus: D8.4 (K), J9.1 (VBUS); also elsewhere on the board
/PA_Power/VGG_PA: R21.2; also elsewhere on the board
/PA_Power/VI2C: J3.4; also elsewhere on the board
/PA_Protection/ADC_Fwd: C43.1, R26.1, R30.2, U13.4 (PA03)
/PA_Protection/ADC_Rev: C50.1, R36.1, R37.2, U13.5 (PA04)
/PA_Protection/ADC_Vgg_PA: R19.1, R21.1, U13.6 (PA05)
/PA_Protection/D+: D8.3 (K), J9.3 (D+), U13.24 (PA25)
/PA_Protection/D-: D8.2 (K), J9.2 (D-), U13.23 (PA24)
/PA_Protection/DRIVER_EN: U13.8 (PA07); also elsewhere on the board
/PA_Protection/Ext_SCL: D5.2 (K), J6.1, R24.2, U13.18 (PA17)
/PA_Protection/Ext_SDA: D5.3 (K), J6.2, R25.2, U13.17 (PA16)
/PA_Protection/Fan PWM: U5.2, U13.19 (PA18)
/PA_Protection/Fan_RPM: J2.3, R11.2, U13.15 (PA14)
/PA_Protection/Pi_RxD: D1.4 (K), J3.3, R18.2, U13.12 (PA09)
/PA_Protection/Pi_TxD: D1.3 (K), J3.2, U13.11 (PA08)
/PA_Protection/TX_Relay: U13.7 (PA06); also elsewhere on the board
/PA_Protection/Temp_INT: R6.2, U2.3 (O.S.), U13.20 (PA19)
/PA_Protection/Tx/Rx: D1.2 (K), J3.1, R16.2, U13.14 (PA11)
/PA_Protection/VFwd: R27.1; also elsewhere on the board
/PA_Protection/VRev: R33.1; also elsewhere on the board
GND: C2.2, C24.2, C37.2, C39.2, C40.2, C43.2, C44.2, C45.2, C48.2, C50.2, C52.2, C53.2, C54.2, D1.1 (A), D5.1 (A), D8.1 (A), D13.1 (K), D14.4 (GND), D15.4 (GND), J2.1, J3.5, J6.4, J9.5 (GND), J10.4, R19.2, R26.2, R29.2, R31.2, R32.2, R34.2, R36.2, R43.2, SW1.2, U2.4 (GND), U2.5 (A2), U2.6 (A1), U2.7 (A0), U5.3 (GND), U12.4 (V-), U13.10 (GND), U13.28 (GND), U15.3 (GND); also elsewhere on the board
unnamed: D6.2 (A), R28.2
unnamed: D6.1 (K), R31.1, U12.2 (-)
unnamed: D10.2 (A), R35.2
unnamed: D10.1 (K), R34.1, U12.6 (-)
unnamed: D13.2 (A), R42.1
unnamed: D14.1 (DIN), U15.4
unnamed: D14.3 (DOUT), D15.1 (DIN)
unnamed: F5.2, F6.2, J2.2
unnamed: J2.4, U5.4
unnamed: D5.4 (K), F2.2, J6.3
unnamed: F3.2, J6.5
unnamed: F4.2, J6.6
unnamed: C53.1, J9.6 (Shield), R43.1
unnamed: J10.2, R44.2, U13.31 (PA30)
unnamed: J10.3, U13.32 (PA31)
unnamed: J10.5, SW1.1, U13.26 (~RESET)
unnamed: R28.1, R30.1, U12.1
unnamed: R35.1, R37.1, U12.7
unnamed: R27.2, R29.1, U12.3 (+)
unnamed: R32.1, R33.2, U12.5 (+)
unnamed: U13.1 (PA00), U15.2
unnamed: R42.2, U13.13 (PA10)
unnamed: C37.1, C45.1, L9.2, U13.9 (VDDANA)
unnamed: C44.1, U13.29 (VDDCORE)
VDC: C52.1, D14.2 (VDD), D15.2 (VDD), U15.5 (VCC); also elsewhere on the board

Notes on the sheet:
OLED Display
I2C Address 0x48
Arduino Pin Mapping ATSAMD21E18 I/O Multiplexer 0 PA00 SK6812 DATA 1 PA03 ADC_FWD 2 PA04 ADC_REV 3 PA05 ADC_VGG 4 PA06 TX_RELAY 5 PA07 DRIVER_EN 6 PA08 SERCOM0 PAD 0 PI_TXD 7 PA09 SERCOM0 PAD 1 PI_RXD 8 PA10 WATCHDOG_LED 9 PA11 PI_TXEN 10 PA14 FAN_RPM 11 PA15 EN_VGG 12 PA16 SERCOM1 PAD 0 EXT_SDA 13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
Temperature Sensor
Raspberry Pi Serial Control Interface
Fan
SWD Program
Compensating RF Detector Buffer Amplifiers
